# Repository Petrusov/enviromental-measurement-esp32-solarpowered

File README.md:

# enviromental-measurement-esp32-solarpowered
This project was created due to the need to create the project as a bachelor's thesis.
The project is focused on the use of a microcontroller ESP32 for collecting data from sensors using communication buses. Data is published through MQTT messages to the MQTT server. Any MQTT client can remove data.

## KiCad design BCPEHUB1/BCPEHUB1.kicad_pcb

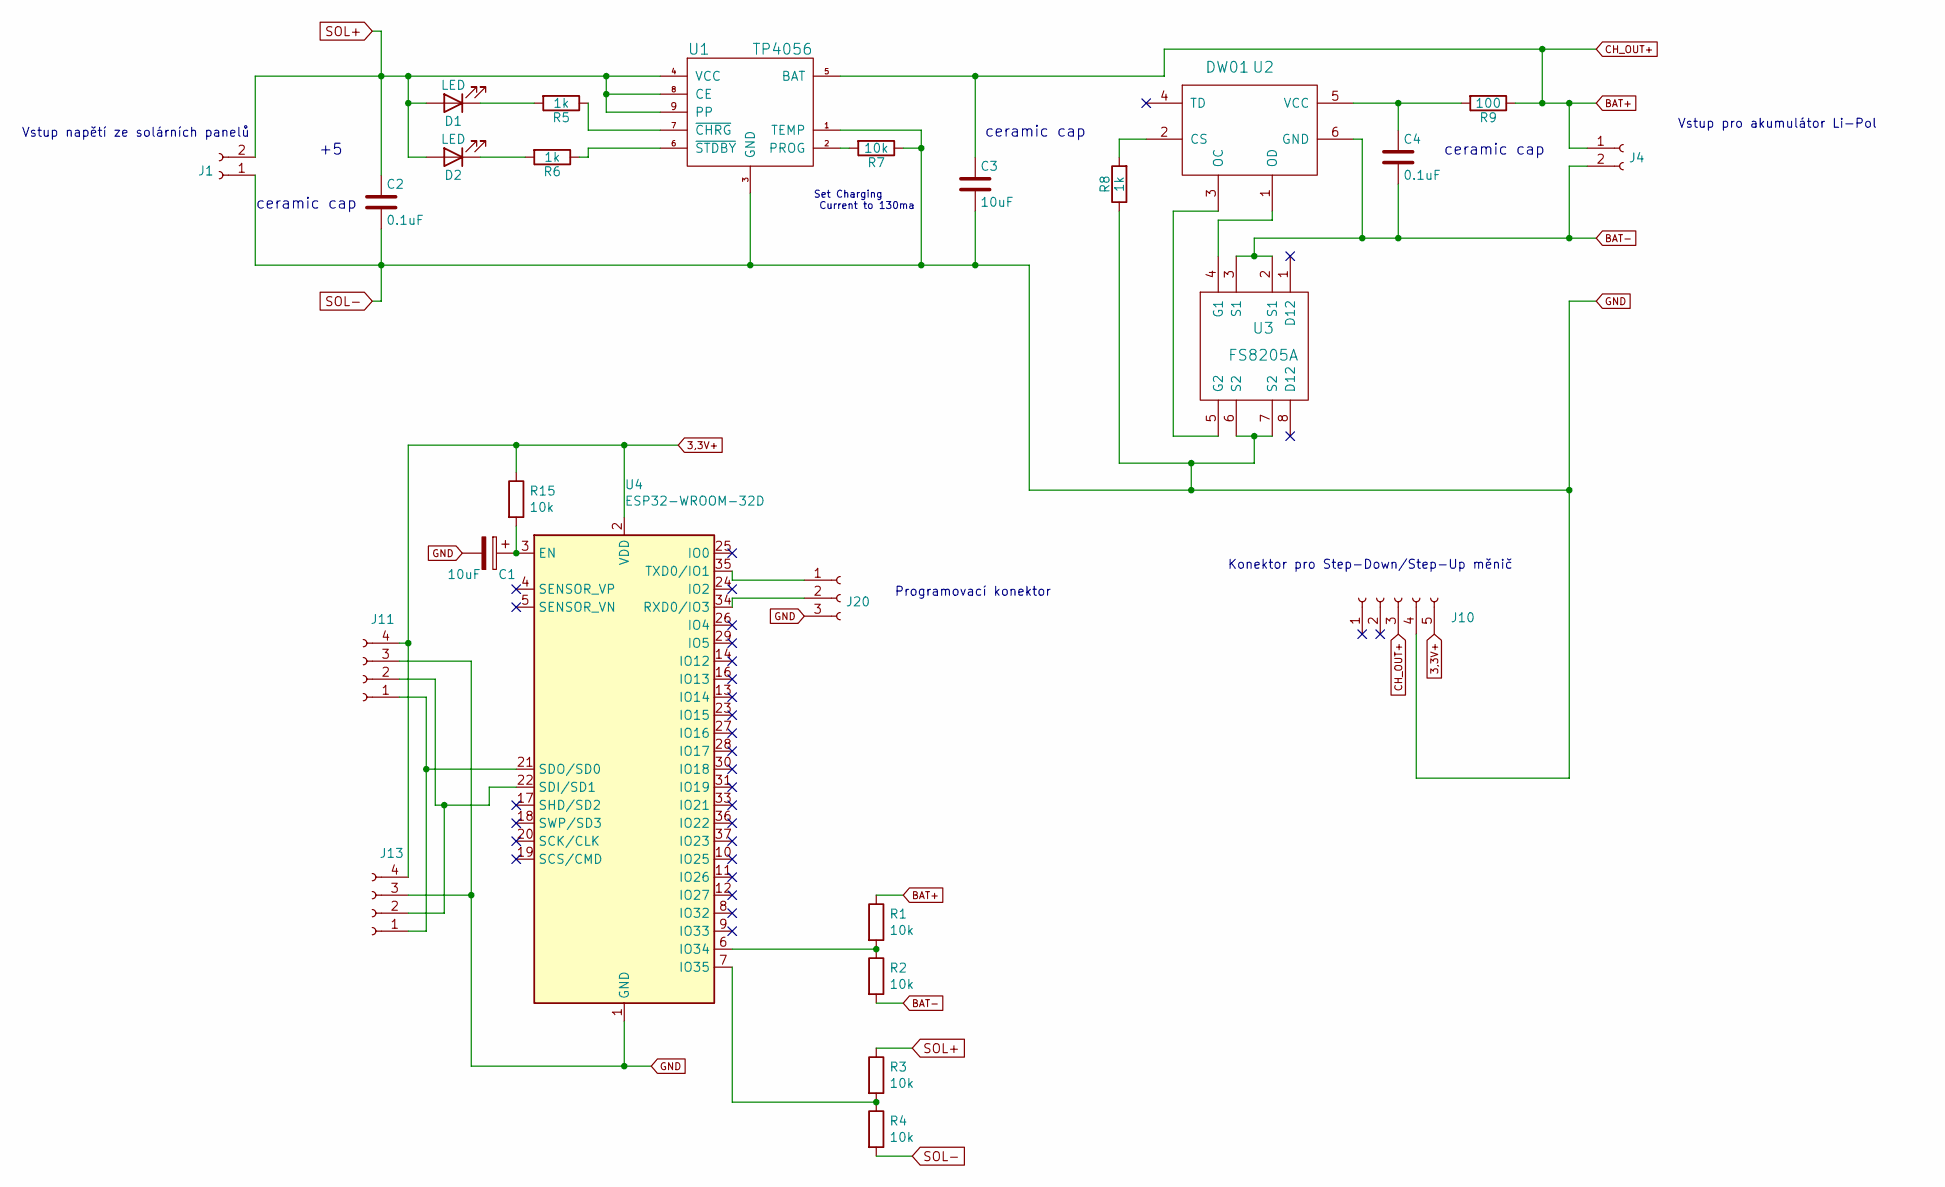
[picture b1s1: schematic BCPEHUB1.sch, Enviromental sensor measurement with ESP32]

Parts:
C1: 10uF; CP_Radial_D4.0mm_P2.00mm
C2: 0.1uF; C_Disc_D3.8mm_W2.6mm_P2.50mm
C3: 10uF; C_Radial_D10.0mm_H12.5mm_P5.00mm
C4: 0.1uF; C_Radial_D10.0mm_H12.5mm_P5.00mm
D1, D2: LED; LED_D1.8mm_W3.3mm_H2.4mm
J1, J4: Conn_01x02_Female; JST_XH_B2B-XH-A_1x02_P2.50mm_Vertical
J10: Conn_01x05_Female; PinSocket_1x05_P2.54mm_Vertical
J11, J13: Conn_01x04_Female; JST_XH_B4B-XH-A_1x04_P2.50mm_Vertical
J20: Conn_01x03_Female; JST_XH_B4B-XH-A_1x04_P2.50mm_Vertical
R1, R2, R3, R4, R7, R15: 10k; R_Axial_DIN0204_L3.6mm_D1.6mm_P7.62mm_Horizontal
R5, R6, R8: 1k; R_Axial_DIN0204_L3.6mm_D1.6mm_P7.62mm_Horizontal
R9: 100; R_Axial_DIN0204_L3.6mm_D1.6mm_P7.62mm_Horizontal
U1: TP4056; TP4056_SOP-8-PP
U2: DW01; SOT23-6
U3: FS8205A; SOP65P640X120-8N
U4: ESP32-WROOM-32D; ESP32-WROOM-32

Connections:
3,3V+: J10.5, J11.4, J13.4, R15.1, U4.2 (VDD)
BAT+: C3.1, J4.1, J10.3, R1.1, R9.1, U1.5 (BAT)
BAT-: C4.2, J4.2, R2.2, U2.6 (GND), U3.2 (S1), U3.3 (S1)
GND: C1.2, C2.2, C3.2, J1.1, J10.4, J11.3, J13.3, J20.3, R4.2, R7.1, R8.1, U1.1 (TEMP), U1.3 (GND), U3.6 (S2), U3.7 (S2), U4.1 (GND), U4.15 (GND), U4.38 (GND), U4.39 (GND)
unnamed: C1.1, R15.2, U4.3 (EN)
unnamed: C4.1, R9.2, U2.5 (VCC)
unnamed: D1.1 (K), R5.2
unnamed: D2.1 (K), R6.2
unnamed: J11.1, J13.1, U4.21 (SDO/SD0)
unnamed: J11.2, J13.2, U4.22 (SDI/SD1)
unnamed: J20.1, U4.35 (TXD0/IO1)
unnamed: J20.2, U4.34 (RXD0/IO3)
unnamed: R1.2, R2.1, U4.6 (IO34)
unnamed: R3.2, R4.1, U4.7 (IO35)
unnamed: R5.1, U1.7 (~CHRG)
unnamed: R6.1, U1.6 (~STDBY)
unnamed: R7.2, U1.2 (PROG)
unnamed: R8.2, U2.2 (CS)
unnamed: U2.1 (OD), U3.4 (G1)
unnamed: U2.3 (OC), U3.5 (G2)
SOL+: C2.1, D1.2 (A), D2.2 (A), J1.2, R3.1, U1.4 (VCC), U1.8 (CE), U1.9 (PP)

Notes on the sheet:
Set Charging Current to 130ma
ceramic cap
Konektor pro Step-Down/Step-Up měnič
Vstup napětí ze solárních panelů
Vstup pro akumulátor Li-Pol
Programovací konektor

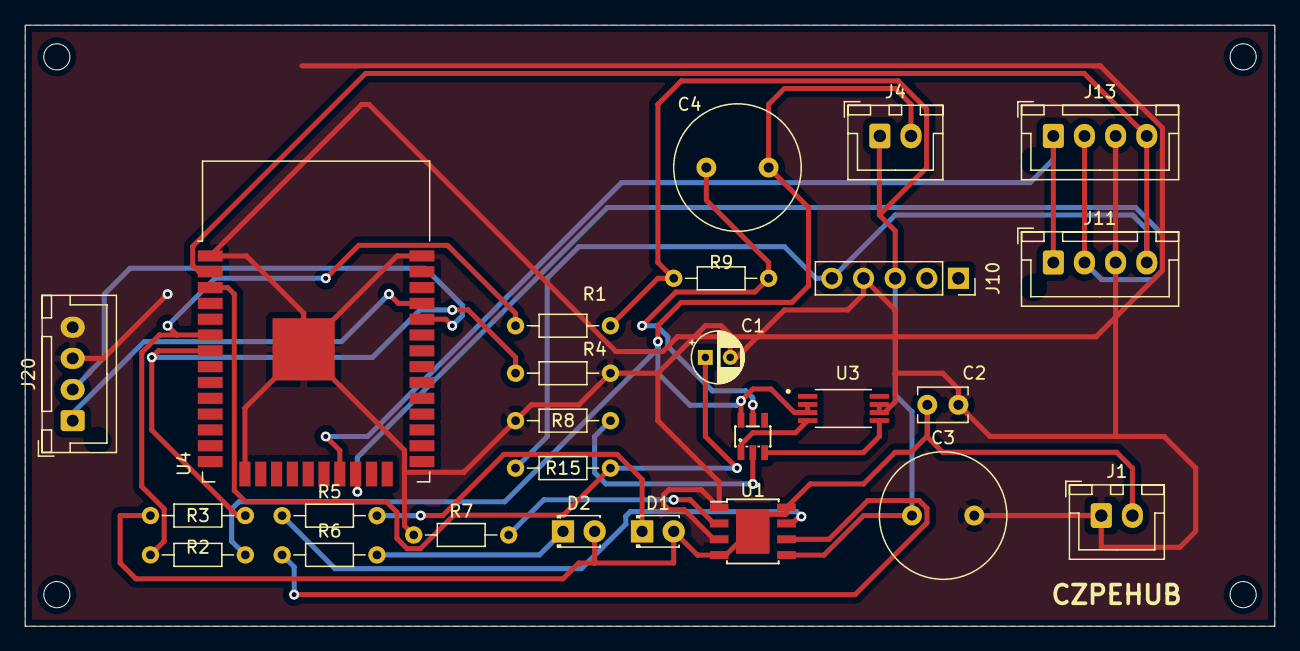
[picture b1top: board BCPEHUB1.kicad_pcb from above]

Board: 2 copper layers, 100.3 x 48.3 mm, 26 parts (0 on the bottom side), 21 nets.
